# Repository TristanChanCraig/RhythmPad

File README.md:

# RhythmPad
***
RhythmPad is a 2x8 macro pad that includes 7 key switches, a rotary encoder switch, an OLED display, and 7 SK6812MINI-E LEDs. I created the case on Onshape and used QMK firmware. The macropad serves to function as a rhythm game pad but also a soundboard as well.

## Features
***
- 7 MX-style key switches
- 1 EC11 rotary encoder switch
- 1 0.91 inch OLED display
- 7 SK6812MINI-E LEDs
- 2 layer case attached with 4 M3x16mm screws and 4 M3x5mx4mm heatset inserts

## Schematic
***
The schematic was made in KiCad and features a switch matrix to lessen the amount of pins the switches take up.

## PCB
***
The pcb was difficult to wire and had many errors due to the LEDS. I probably should've had better placements before wiring.

## CAD
***
The case was designed in OnShape and uses the 4 M3x16mm screws and 4 M3x5mx4mm heatset inserts. It was hard to import the switch blueprint to make sure each square had enough space. It was also time-consuming to constantly switch between the pcb in KiCad and Onshape to measure each dimension to make sure it fit.

## Firmware
***
This was the hardest part as QMK needed its environment to be downloaded which took a lot of time. It was also really confusing to work through the keyboard, config, and rules files but it worked in the end.

## BOM
***
- 1 Seeed XIAO RP2040
- 8x 1N4148 Diodes
- 7x MX-Style switches
- 1x EC11 Rotary encoders
- 1x 0.91 inch OLED display 
- 7x white blank DSA keycaps
- 7x SK6812 MINI-E LEDs
- 4x M3x16mm screws
- 4x M3x5mx4mm heatset inserts
- 1x Case (Top layer and bottom layer)
- 1x PCB (Custom-made)

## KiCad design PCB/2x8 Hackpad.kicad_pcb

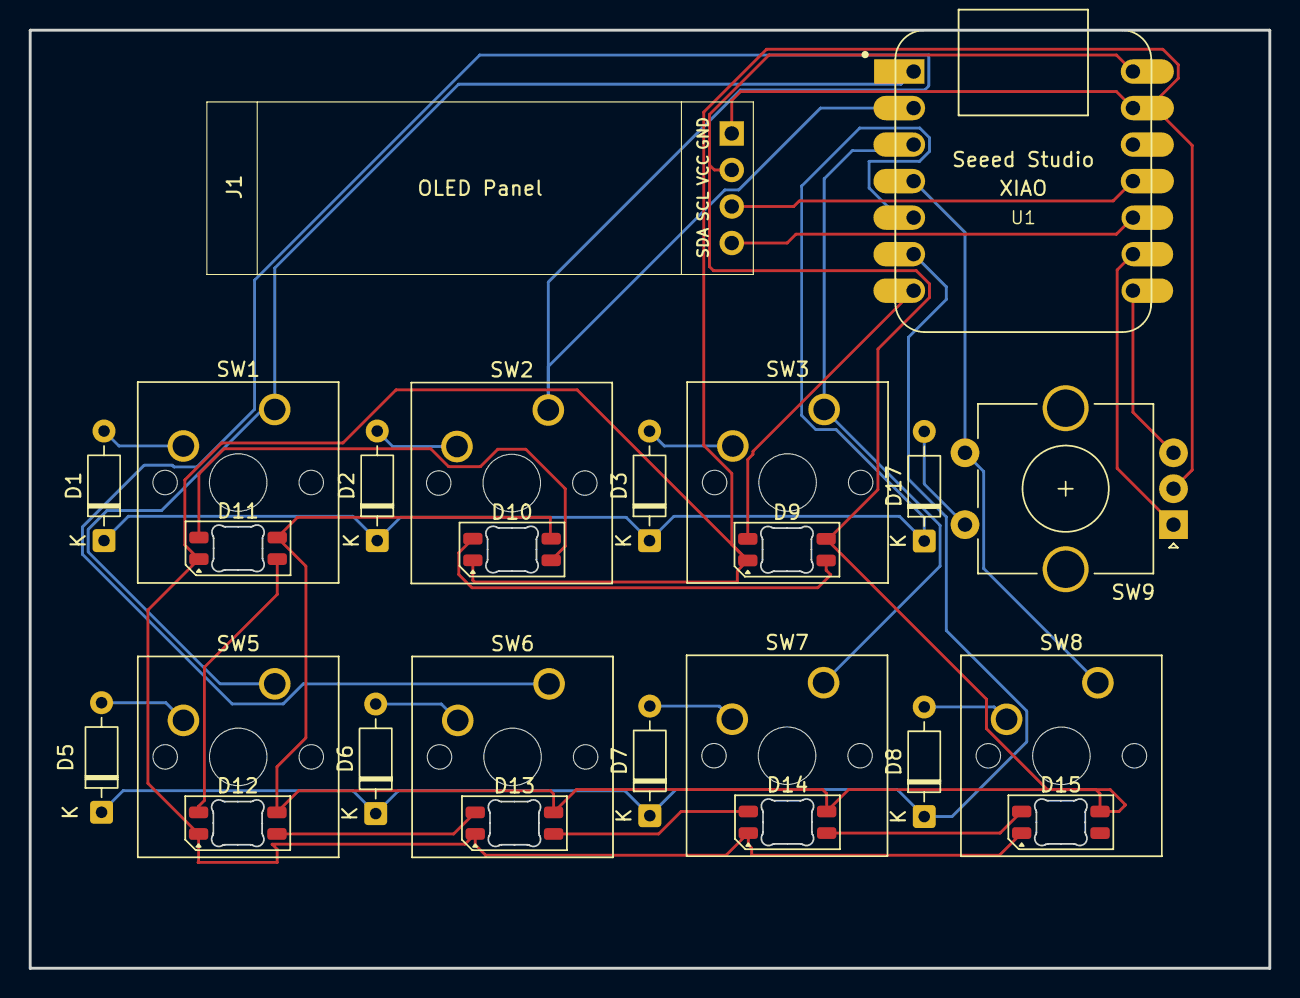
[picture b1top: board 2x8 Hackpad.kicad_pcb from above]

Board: 2 copper layers, 86.2 x 65.2 mm, 25 parts (0 on the bottom side), 27 nets.

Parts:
D1, D2, D3, D5, D6, D7, D8, D17: 1N4148; D_DO-35_SOD27_P7.62mm_Horizontal
D9, D10, D11, D12, D13, D14, D15: SK6812MINI-E; LED_SK6812MINI-E_3.2x2.8mm_P1.5mm_ReverseMount
J1: Conn_01x04_Pin; OLED_DISPLAY
SW1, SW2, SW3, SW5, SW6, SW7, SW8: SW_Push; SW_Cherry_MX_1.00u_PCB
SW9: RotaryEncoder_Switch; RotaryEncoder_Alps_EC11E-Switch_Vertical_H20mm_CircularMoun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
U1: MOUDLE-SEEEDUINO-XIAO; XIAO-Generic-Hybrid-14P-2.54-21X17.8MM

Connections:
+5V: D9.3 (VDD), D10.3 (VDD), D11.3 (VDD), D12.3 (VDD), D13.3 (VDD), D14.3 (VDD), D15.3 (VDD), J1.2, U1.14 (5V)
/Col 0: SW1.1, SW5.1, U1.1 (PA02_A0_D0)
/Col 1: SW2.1, SW6.1, U1.2 (PA4_A1_D1)
/Col 2: SW3.1, SW7.1, U1.3 (PA10_A2_D2)
/Col 3: SW8.1, SW9.S1, U1.4 (PA11_A3_D3)
/EC11A: SW9.A, U1.9 (PA7_A8_D8_SCK)
/EC11B: SW9.B, U1.8 (PB09_A7_D7_RX)
/ECC11SWA: D17.2 (A), SW9.S2
/LED: D9.2 (DIN), U1.7 (PB08_A6_D6_TX)
/Row 0: D1.1 (K), D2.1 (K), D3.1 (K), D17.1 (K), U1.5 (PA8_A4_D4_SDA)
/Row 1: D5.1 (K), D6.1 (K), D7.1 (K), D8.1 (K), U1.6 (PA9_A5_D5_SCL)
/SCL: J1.4, U1.10 (PA5_A9_D9_MISO)
/SDA: J1.3, U1.11 (PA6_A10_D10_MOSI)
GND: D9.1 (VSS), D10.1 (VSS), D11.1 (VSS), D12.1 (VSS), D13.1 (VSS), D14.1 (VSS), D15.1 (VSS), J1.1, SW9.C, U1.13 (GND)
unnamed: D1.2 (A), SW1.2
unnamed: D2.2 (A), SW2.2
unnamed: D3.2 (A), SW3.2
unnamed: D5.2 (A), SW5.2
unnamed: D6.2 (A), SW6.2
unnamed: D7.2 (A), SW7.2
unnamed: D8.2 (A), SW8.2
unnamed: D9.4 (DOUT), D10.2 (DIN)
unnamed: D10.4 (DOUT), D11.2 (DIN)
unnamed: D11.4 (DOUT), D12.2 (DIN)
unnamed: D12.4 (DOUT), D13.2 (DIN)
unnamed: D13.4 (DOUT), D14.2 (DIN)
unnamed: D14.4 (DOUT), D15.2 (DIN)

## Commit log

2026-06-26 Create Assets
2026-06-26 Create CAD
2026-06-26 Create Temp
